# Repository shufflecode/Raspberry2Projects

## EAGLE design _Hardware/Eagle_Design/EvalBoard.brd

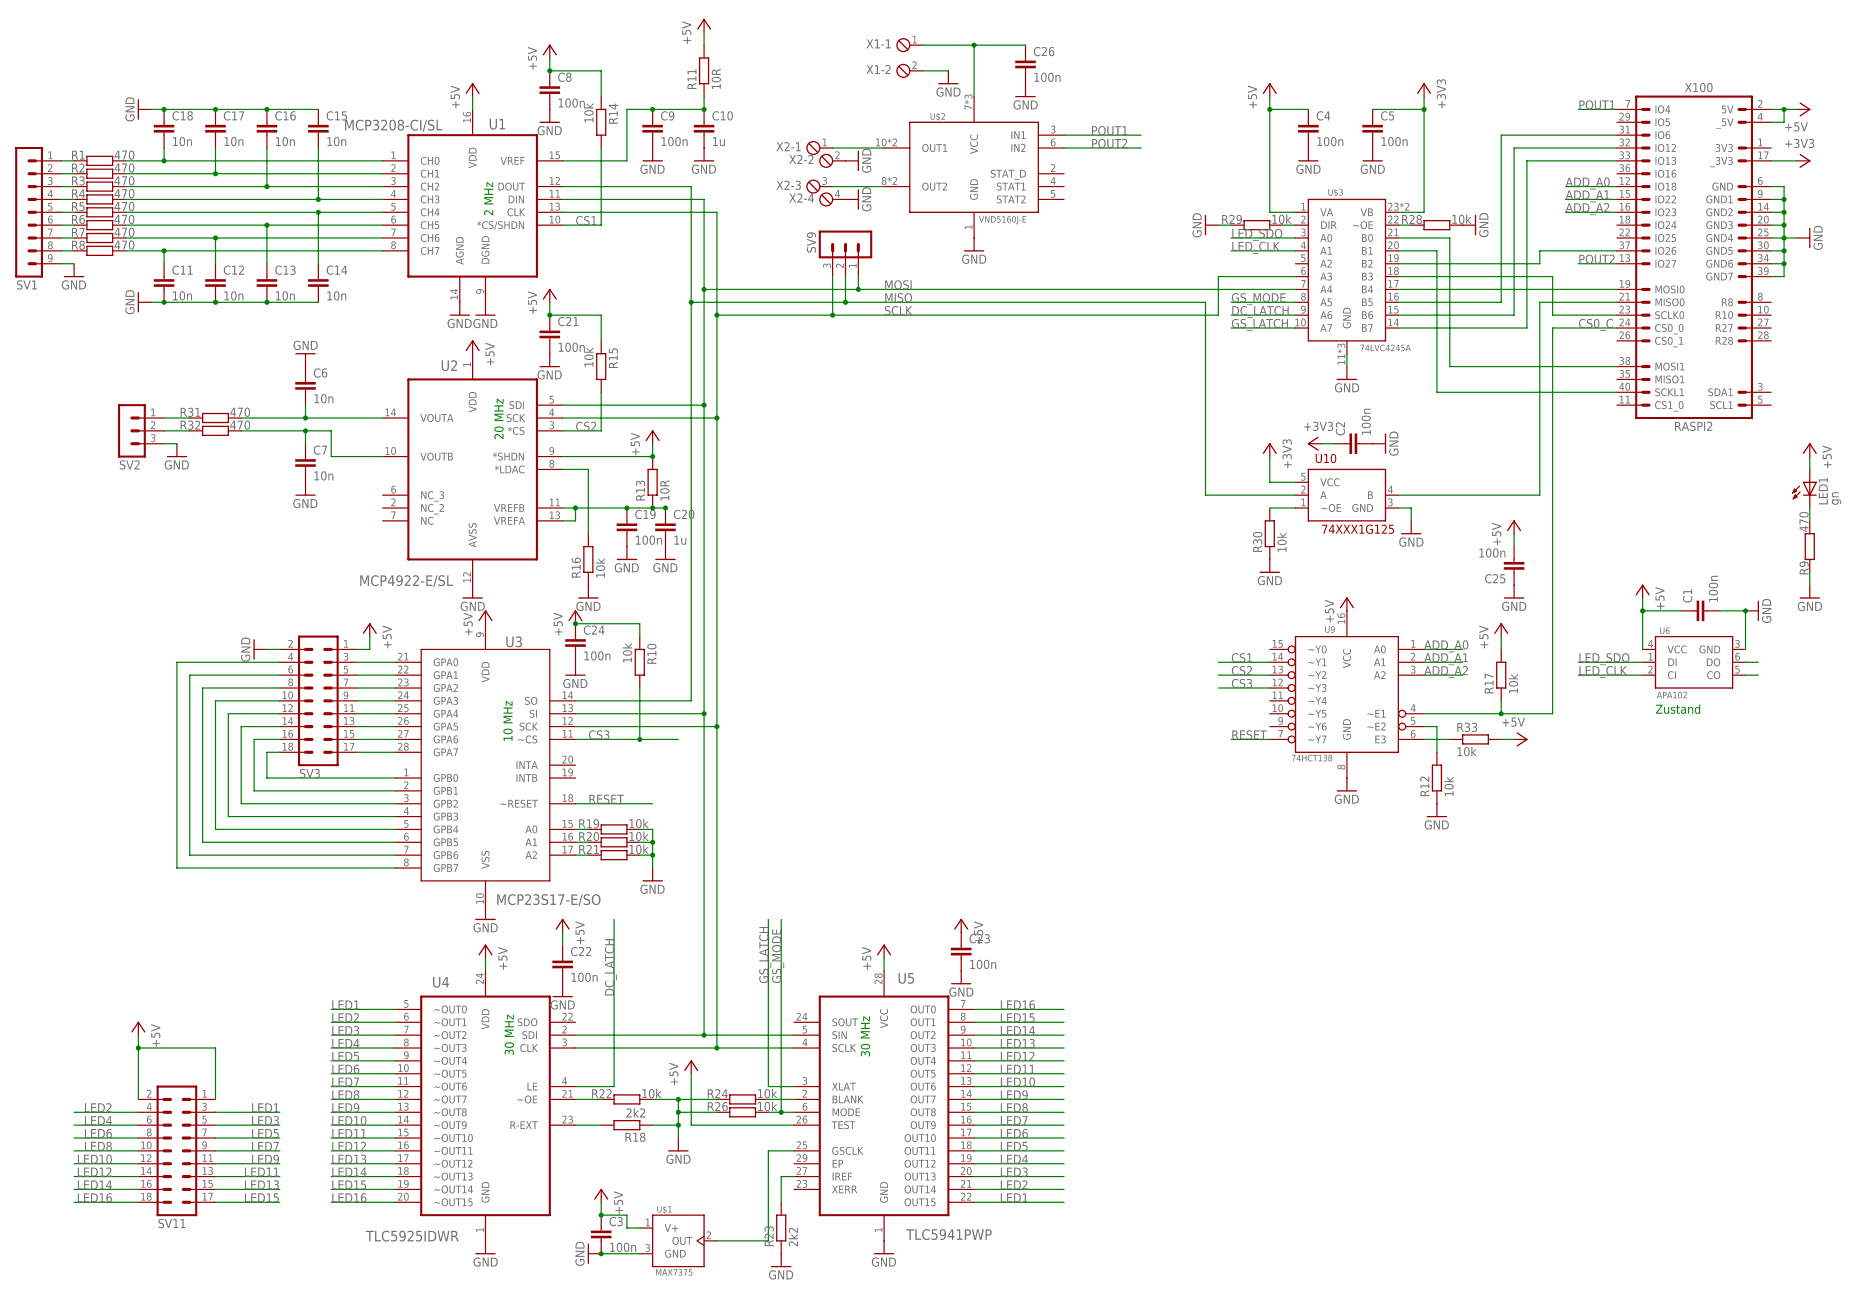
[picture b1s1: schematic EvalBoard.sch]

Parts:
C1, C2, C3, C4, C5, C8, C9, C19, C21, C22, C23, C24, C25, C26: 100n; C0805
C6, C7, C11, C12, C13, C14, C15, C16, C17, C18: 10n; C0805
C10, C20: 1u; C0805
LED1: gn; LED5MM
R1, R2, R3, R4, R5, R6, R7, R8, R9, R31, R32: 470; R0805
R10, R12, R14, R15, R16, R17, R19, R20, R21, R22, R24, R26, R28, R29, R30, R33: 10k; R0805
R11, R13: 10R; R0805
R18, R23: 2k2; R0805
SV1: MA09-1W
SV2, SV9: MA03-1
SV3, SV11: MA09-2W
U1: MCP3208-CI/SL; SOIC127P600X175-16N
U2: MCP4922-E/SL; SOIC127P600X175-14N
U3: MCP23S17-E/SO; SOIC127P030X265-28N
U4: TLC5925IDWR; SOIC127P1030X265-24N
U5: TLC5941PWP; SOP65P640X120-29N
U6: APA102; LED5050PACK
U9: 74HCT138; SOIC127P600X175-16N
U10: 74XXX1G125; SOT23-5L
U$1: MAX7375; SC70
U$2: VND5160J-E; POWERSSO12
U$3: 74LVC4245A; SOIC127P1030X265-24N
X1: MPT2; 2POL254
X2: MPT4; 4POL254
X100: RASPI2; ML40

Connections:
+3V3: C2.1, C5.1, U10.5 (VCC), U$3.23 (VB), U$3.24 (VB), X100.17 (_3V3)
+5V: C1.1, C3.1, C4.1, C8.1, C21.1, C22.1, C23.1, C24.1, C25.2, LED1.A, R10.1, R11.2, R13.2, R14.1, R15.1, R17.2, R33.2, SV3.1, SV11.1, SV11.2, U1.16 (VDD), U2.1 (VDD), U2.9 (*SHDN), U3.9 (VDD), U4.24 (VDD), U5.26 (TEST), U5.28 (VCC), U6.4 (VCC), U9.16 (VCC), U$1.1 (V+), U$3.1 (VA), X100.2 (5V), X100.4 (_5V)
ADD_A0: U9.1 (A0), X100.12 (IO18)
ADD_A1: U9.2 (A1), X100.15 (IO22)
ADD_A2: U9.3 (A2), X100.16 (IO23)
CS0_C: R17.1, U9.4 (~E1), X100.24 (CS0_0)
CS1: R14.2, U1.10 (*CS/SHDN), U9.14 (~Y1)
CS2: R15.2, U2.3 (*CS), U9.13 (~Y2)
CS3: R10.2, U3.11 (~CS), U9.12 (~Y3)
DC_LATCH: U4.4 (LE), U$3.9 (A6)
GND: C1.2, C2.2, C3.2, C4.2, C5.2, C6.1, C7.2, C8.2, C9.2, C10.2, C11.2, C12.2, C13.2, C14.2, C15.1, C16.1, C17.1, C18.1, C19.2, C20.2, C21.2, C22.2, C23.2, C24.2, C25.1, C26.2, R9.1, R12.1, R16.1, R18.1, R19.2, R20.2, R21.2, R22.2, R23.1, R24.1, R26.1, R28.2, R29.1, R30.1, SV1.9, SV2.3, SV3.2, U1.9 (DGND), U1.14 (AGND), U2.12 (AVSS), U3.10 (VSS), U4.1 (GND), U5.1 (GND), U6.3 (GND), U9.8 (GND), U10.3 (GND), U$1.3 (GND), U$2.1 (GND), U$3.11 (GND), U$3.12 (GND), U$3.13 (GND), X1.2, X2.2, X2.4, X100.6 (GND), X100.9 (GND1), X100.14 (GND2), X100.20 (GND3), X100.25 (GND4), X100.30 (GND5), X100.34 (GND6), X100.39 (GND7)
GS_LATCH: U5.3 (XLAT), U$3.10 (A7)
GS_MODE: R26.2, U5.6 (MODE), U$3.8 (A5)
LED1: SV11.3, U4.5 (~OUT0), U5.22 (OUT15)
LED2: SV11.4, U4.6 (~OUT1), U5.21 (OUT14)
LED3: SV11.5, U4.7 (~OUT2), U5.20 (OUT13)
LED4: SV11.6, U4.8 (~OUT3), U5.19 (OUT12)
LED5: SV11.7, U4.9 (~OUT4), U5.18 (OUT11)
LED6: SV11.8, U4.10 (~OUT5), U5.17 (OUT10)
LED7: SV11.9, U4.11 (~OUT6), U5.16 (OUT9)
LED8: SV11.10, U4.12 (~OUT7), U5.15 (OUT8)
LED9: SV11.11, U4.13 (~OUT8), U5.14 (OUT7)
LED10: SV11.12, U4.14 (~OUT9), U5.13 (OUT6)
LED11: SV11.13, U4.15 (~OUT10), U5.12 (OUT5)
LED12: SV11.14, U4.16 (~OUT11), U5.11 (OUT4)
LED13: SV11.15, U4.17 (~OUT12), U5.10 (OUT3)
LED14: SV11.16, U4.18 (~OUT13), U5.9 (OUT2)
LED15: SV11.17, U4.19 (~OUT14), U5.8 (OUT1)
LED16: SV11.18, U4.20 (~OUT15), U5.7 (OUT0)
LED_CLK: U6.2 (CI), U$3.4 (A1)
LED_SDO: U6.1 (DI), U$3.3 (A0)
MISO: SV9.2, U1.12 (DOUT), U3.14 (SO), U10.2 (A)
MISO0: U10.4 (B), X100.21 (MISO0)
MOSI: SV9.1, U1.11 (DIN), U2.5 (SDI), U3.13 (SI), U4.2 (SDI), U5.5 (SIN), U$3.7 (A4)
MOSI0: U$3.17 (B4), X100.19 (MOSI0)
MOSI1: U$3.21 (B0), X100.38 (MOSI1)
unnamed: R1.1, SV1.1
unnamed: R2.1, SV1.2
unnamed: R3.1, SV1.3
unnamed: R4.1, SV1.4
unnamed: R5.1, SV1.5
unnamed: R6.1, SV1.6
unnamed: R7.1, SV1.7
unnamed: R8.1, SV1.8
unnamed: C18.2, R1.2, U1.1 (CH0)
unnamed: C17.2, R2.2, U1.2 (CH1)
unnamed: C16.2, R3.2, U1.3 (CH2)
unnamed: C15.2, R4.2, U1.4 (CH3)
unnamed: C14.1, R5.2, U1.5 (CH4)
unnamed: C13.1, R6.2, U1.6 (CH5)
unnamed: C12.1, R7.2, U1.7 (CH6)
unnamed: C11.1, R8.2, U1.8 (CH7)
unnamed: C6.2, R31.2, U2.14 (VOUTA)
unnamed: R33.1, U9.6 (E3)
unnamed: R30.2, U10.1 (~OE)
unnamed: U$3.19 (B2), X100.37 (IO26)
unnamed: R31.1, SV2.1
unnamed: R32.1, SV2.2
unnamed: C7.1, R32.2, U2.10 (VOUTB)
unnamed: U$3.16 (B5), X100.31 (IO6)
unnamed: LED1.K (C), R9.2
unnamed: U$2.8 (OUT2), U$2.9 (OUT2), X2.3
unnamed: U$2.10 (OUT1), U$2.11 (OUT1), X2.1
unnamed: C9.1, C10.1, R11.1, U1.15 (VREF)
unnamed: C19.1, C20.1, R13.1, U2.11 (VREFB), U2.13 (VREFA)
unnamed: R16.2, U2.8 (*LDAC)
unnamed: R18.2, U4.23 (R-EXT)
unnamed: U5.25 (GSCLK), U$1.2 (OUT)
unnamed: U$3.15 (B6), X100.32 (IO12)
unnamed: R19.1, U3.15 (A0)
unnamed: R20.1, U3.16 (A1)
unnamed: R21.1, U3.17 (A2)
unnamed: U$3.14 (B7), X100.33 (IO13)
unnamed: R22.1, U4.21 (~OE)
unnamed: R12.2, U9.5 (~E2)
unnamed: R23.2, U5.27 (IREF)
unnamed: R24.2, U5.2 (BLANK)
unnamed: R28.1, U$3.22 (~OE)
unnamed: R29.2, U$3.2 (DIR)
PA0: SV3.3, U3.21 (GPA0)
PA1: SV3.5, U3.22 (GPA1)
PA2: SV3.7, U3.23 (GPA2)
PA3: SV3.9, U3.24 (GPA3)
PA4: SV3.11, U3.25 (GPA4)
PA5: SV3.13, U3.26 (GPA5)
PA6: SV3.15, U3.27 (GPA6)
PA7: SV3.17, U3.28 (GPA7)
PB0: SV3.18, U3.1 (GPB0)
PB1: SV3.16, U3.2 (GPB1)
PB2: SV3.14, U3.3 (GPB2)
PB3: SV3.12, U3.4 (GPB3)
PB4: SV3.10, U3.5 (GPB4)
PB5: SV3.8, U3.6 (GPB5)
PB6: SV3.6, U3.7 (GPB6)
PB7: SV3.4, U3.8 (GPB7)
POUT1: U$2.3 (IN1), X100.7 (IO4)
POUT2: U$2.6 (IN2), X100.13 (IO27)
RESET: U3.18 (~RESET), U9.7 (~Y7)
SCLK: SV9.3, U1.13 (CLK), U2.4 (SCK), U3.12 (SCK), U4.3 (CLK), U5.4 (SCLK), U$3.6 (A3)
SCLK0: U$3.18 (B3), X100.23 (SCLK0)
SCLK1: U$3.20 (B1), X100.40 (SCKL1)
VCC: C26.1, U$2.7 (VCC), U$2.12 (VCC), U$2.TP (VCC), X1.1

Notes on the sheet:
Zustand
2 MHz
20 MHz
10 MHz
30 MHz

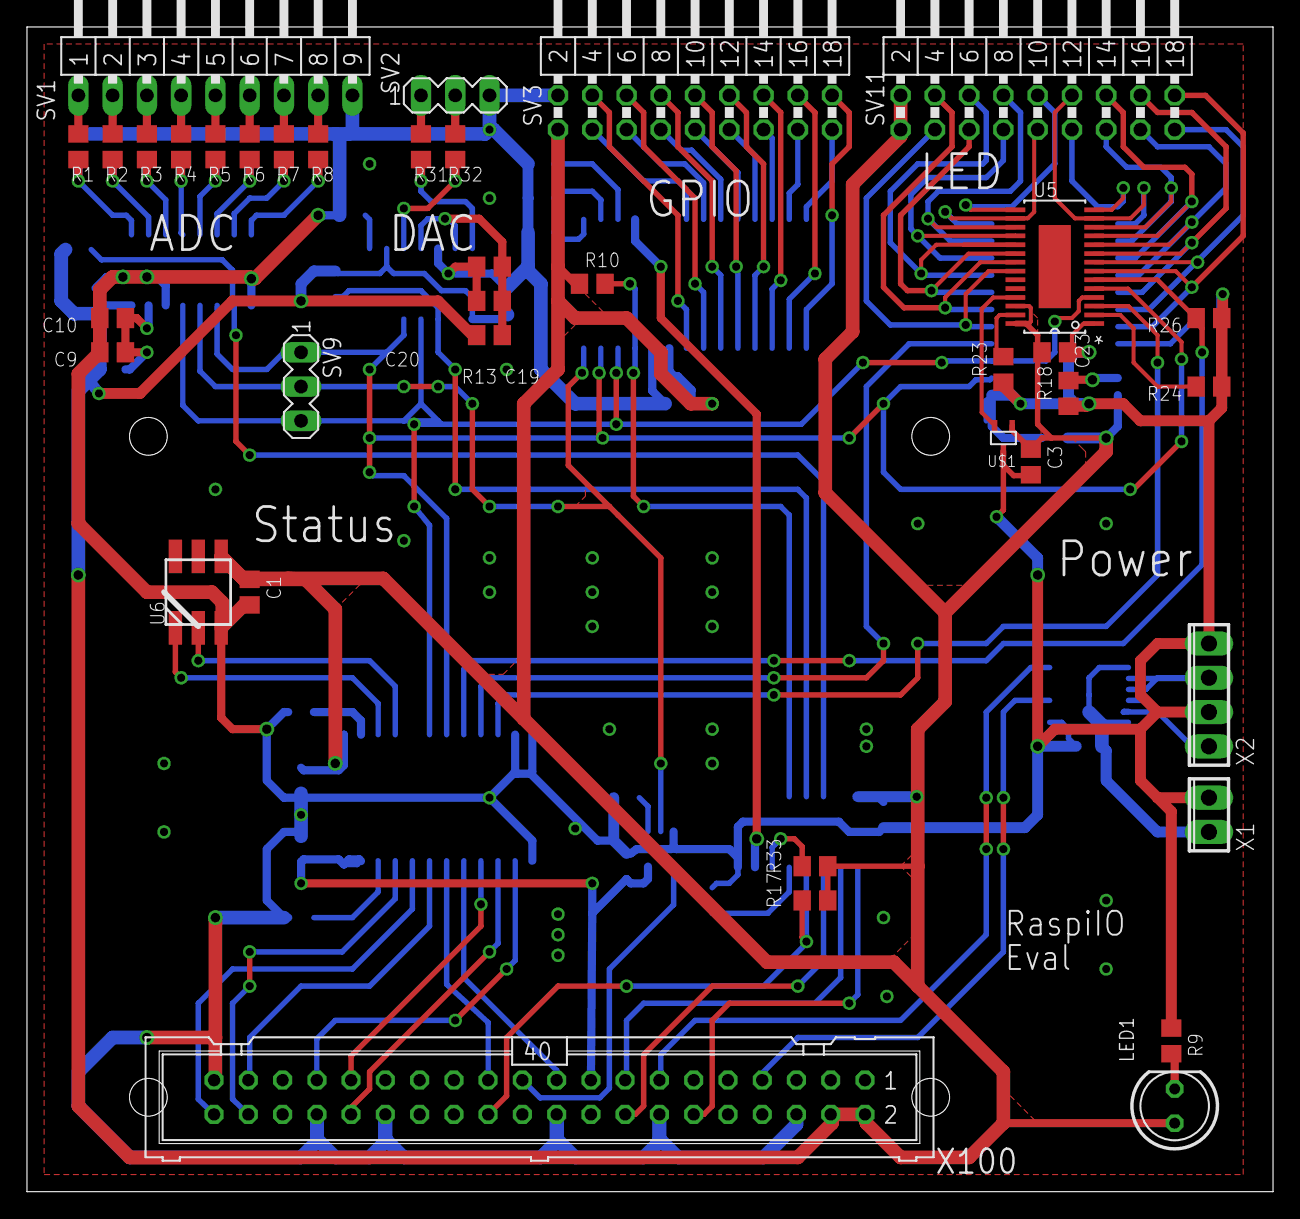
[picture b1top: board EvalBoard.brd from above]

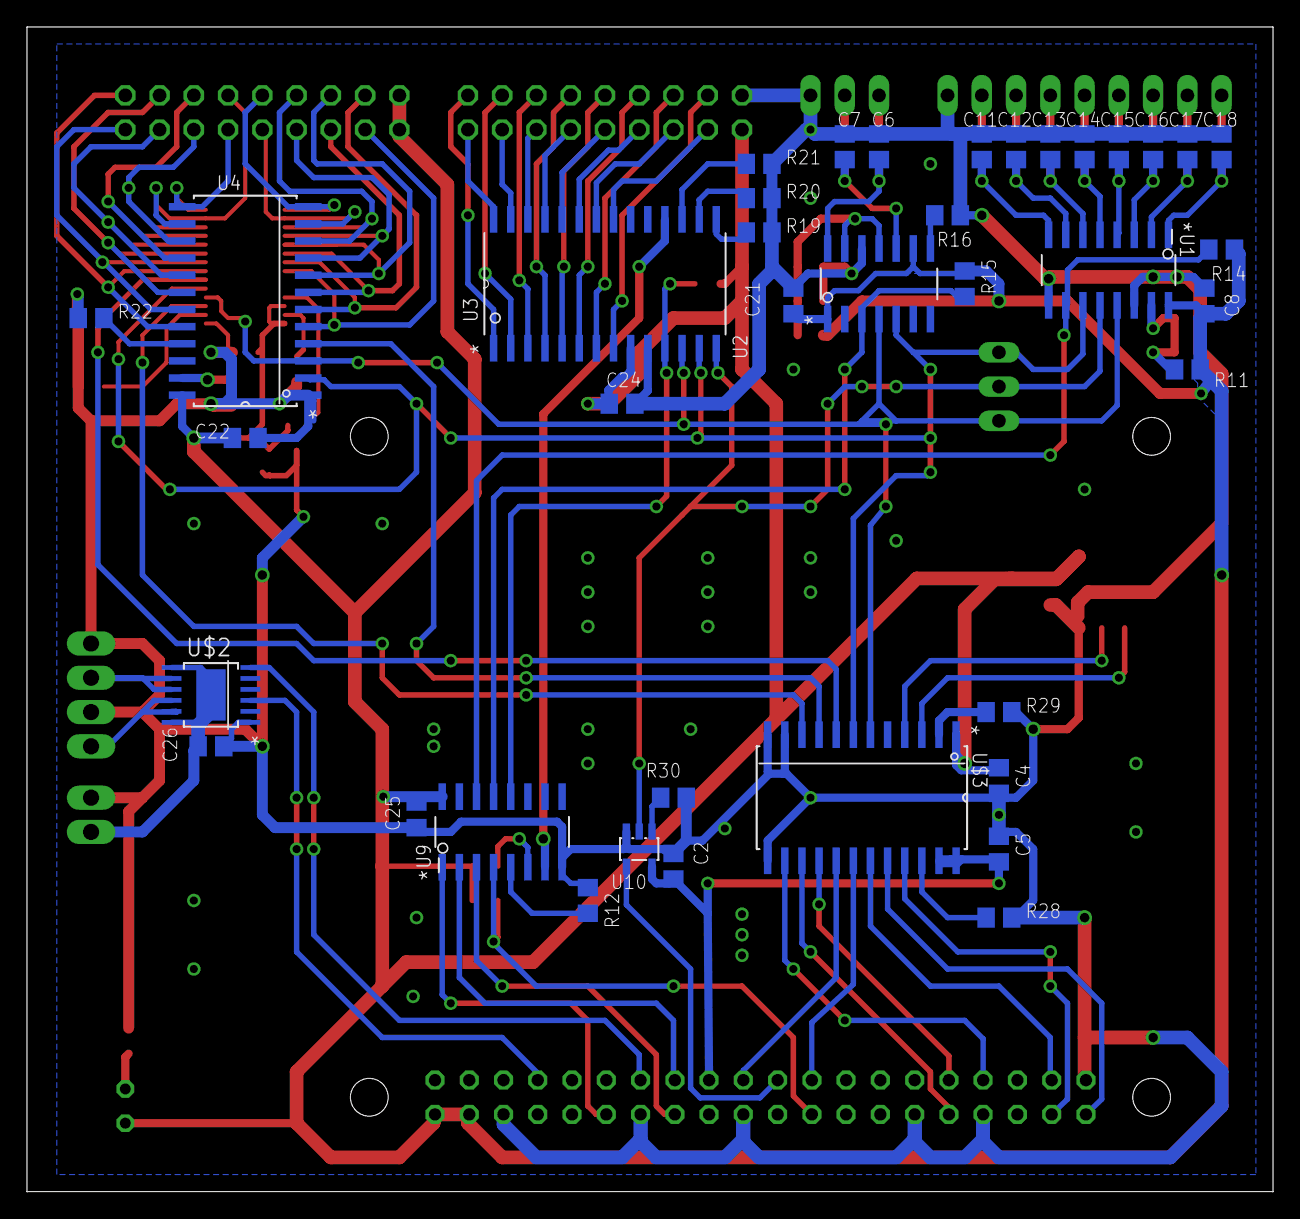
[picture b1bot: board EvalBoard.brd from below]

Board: 2 copper layers, 92.4 x 86.3 mm, 77 parts (39 on the bottom side), 102 nets.

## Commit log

2015-11-28 Created team project folder $/Raspi2Team via the Team Project Creation Wizard
2015-11-28 Checking in new Team Foundation Build Automation files.
2015-11-28 Check-in the Lab default template
2015-11-28 test
2016-01-12 hardware nazu ;)
2016-01-12 Hardware dazu ;-)
2016-01-12 Demo-Projekt für die IO-Geschichte
2016-01-12 Der Harwareteil ...
2016-01-12 Funktionierender Demo-Stand
2016-01-12 LED-Eval-Demo hinzugefügt (wird bald wieder gelöscht).
2016-01-14 Basic tests with Api
2016-01-15 comments, refactoring, things moved to files
2016-01-15 Auf das Neue Treibermodell umgestellt.
2016-01-15 Eval-Klasse gelöscht
2016-01-15 Bugfix Paramter Handling
2016-01-15 changes because of jakob ;)
2016-01-16 Renamed WebServer to SmartHomeController
2016-01-25 Rechtschreibfehler. GPIO um Pullups und Input Logic erweiter (siehe auch IO-Demo). LED treiber um Refresh-Routine erweiter (funktioniert aber noch nicht ganz). Bugfix folgt ...
2016-01-25 Weitere LED-Definition. Grundzüge für Pattern Generator für LED-Streifen
2016-01-25 weitere Features für GPIO ... LED-Treiber funktioniert noch nicht ganz.
2016-01-26 GrayScale LED-Treiber funktioniert nun prinzipiell)
2016-02-17 Nachrichten-Objekt-Definitoin für Zyklischen und Azyklischen Datenaustausch hinzugefügt
2016-02-18 Einstellungen und Ordnung
2016-04-05 ToDo Eintrag
2016-04-05 Hall-Drucktaster-Testprojekt
2016-04-05 Unnötiges Server-Client-Objekt gelöscht
2016-04-05 Weitere Kommando-Flag eingebaut
2016-04-05 Code Aus Demo-Applikation eingebaut ... Hardware-Funktionen müssten nun gehen.
2016-04-08 LED-Streifen-Demo ... noch unkommentiert
2016-04-08 RGB-Streifen eingebaut ... bereit zum Test
2016-04-08 Server Client auch mit LED-Streifen einsetzbar
2016-04-17 RGB-LED-Auf 8bit umgestellt
2016-04-17 LED-Streifen Demo wegen 8-bit-Umstellung nachgezogen
2016-04-17 RGB-Streifen-Funktionslib ist nun testweise einsatzbereit
2016-06-01 Projektdatei hinzugefühgt
2017-10-16 Migrated from vsts
2017-10-16 moved directory structure (level up!)
2017-10-16 added .gitignore File
2017-10-23 Documentation for IO-EvalBoard added
2023-10-03 Bump Newtonsoft.Json from 7.0.1 to 13.0.1 in /AppWpf
    Bumps [Newtonsoft.Json](https://github.com/JamesNK/Newtonsoft.Json) from 7.0.1 to 13.0.1.
    - [Release notes](https://github.com/JamesNK/Newtonsoft.Json/releases)
    - [Commits](https://github.com/JamesNK/Newtonsoft.Json/compare/7.0.1...13.0.1)
    ---
    updated-dependencies:
    - dependency-name: Newtonsoft.Json
2023-10-03 Bump Newtonsoft.Json from 8.0.2 to 13.0.1 in /AppWpfSimpleClient
    Bumps [Newtonsoft.Json](https://github.com/JamesNK/Newtonsoft.Json) from 8.0.2 to 13.0.1.
    - [Release notes](https://github.com/JamesNK/Newtonsoft.Json/releases)
    - [Commits](https://github.com/JamesNK/Newtonsoft.Json/compare/8.0.2...13.0.1)
    ---
    updated-dependencies:
    - dependency-name: Newtonsoft.Json
